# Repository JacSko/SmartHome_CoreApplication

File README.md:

# SmartHome CoreApplication

## Description
The idea of the project is to gain simple control over home appliance (like lighting).
Main board was desgined to use STM32F411CEU MCU. It communicates with other boards (list below) using different interfaces (I2C, OneWire, USART).
The main responsibility of this part of project is to ensure informations about current temperature and humidity and appliance state.

**Main board is connected with:**
- **Relays board** - equipped with 16 relays, supports either 12VDC and 230VAC switching. Board allows to e.g control light state in all rooms. Connection over I2C bus.
- **Inputs board** - board designed to handle 16 inputs (8x 12VDC, 8x 230VAC). Connection over I2C bus with interrupt fired on each input state changed. The bouncing of inputs state has been resolved either by adding debouce capacitor and programatically, by delaying inputs state readout.
- **LED's board** - board equipped with 16 outputs to control led ambient light on staircase placed near to steps. It allows to achieve some lighting effects since can be controlled independently.
- **Sensors board** - Board, where temperature and humidity sensors (DHT11/DHT22 - type is auto-detected in application), also light intense sensor is connected. The communication is realized over OneWire interface, when light intense sensor signal is send in pure analogue form.

## Details
This module is not able to present gathered data.
There is another project [SmartHome_RPi](https://github.com/JacSko/SmartHome_RPi) responsible for presenting received data.
The communication with CoreApplication can be done in two ways:
- **Over WiFi** - ESP01 module is onboard, on startup it creates TCP server, where the RaspberryPi can connects and gets the data. Messages are send in raw bytes mode (for protocol specification see notification_manager.h)
- **Over Bluetooth** - this channel is desgined mainly to provide debug traces, but there are several commands that can be issued in string-based, human readable form (see doc/ dirextory for documntation details)

Project build is managed by CMake.
Core application was prepared using CMSIS bare-metal library without dependencies to external libraries (only appropriate header files are required, but those are part of repository).
Project contains also unit tests, where the original MCU header files has been stubbed to allow compilation.

## Building
### Building for target
To build binary, You need to have:
- the arm-none-eabi toolchain
- The st-linkv2 drivers (can be compiled from sources)
- The ST-FLASH utility installed
Once all of those step are ready:
```
cd <project_dir>
mkdir build && cd build
cmake ..
make
```
After the binary can be flashed by issuing:
```
make write
```
### Building Simulation
For details how to use this target, see [SmartHome_Tests](https://github.com/JacSko/SmartHome_Tests)
```
cd <project_dir>
mkdir build_sim
cd build_sim
cmake .. -DSIMULATION=On
make
```
### Building Unit tests
To build unit test, You have to clone googletest repo:
```
cd <project_dir>
cd ext_lib/googletest
git clone https://github.com/google/googletest.git
```
Than run script:
```
./build_and_run_ut.sh
```
### Coverage calculation
Run script:
```
./build_and_run_coverage.sh
```
HTML report will be opened automatically in Firefox, but it can be also found:
```
build_ut/html/coverage.html
```
## TODO
- [ ] EEPROM handling
- [ ] Settings rework to allow read/write settings from EEPROM
- [ ] ADC driver (power supply voltage, light intensity)
- [ ] Flashing over UART (from RaspberryPi module)

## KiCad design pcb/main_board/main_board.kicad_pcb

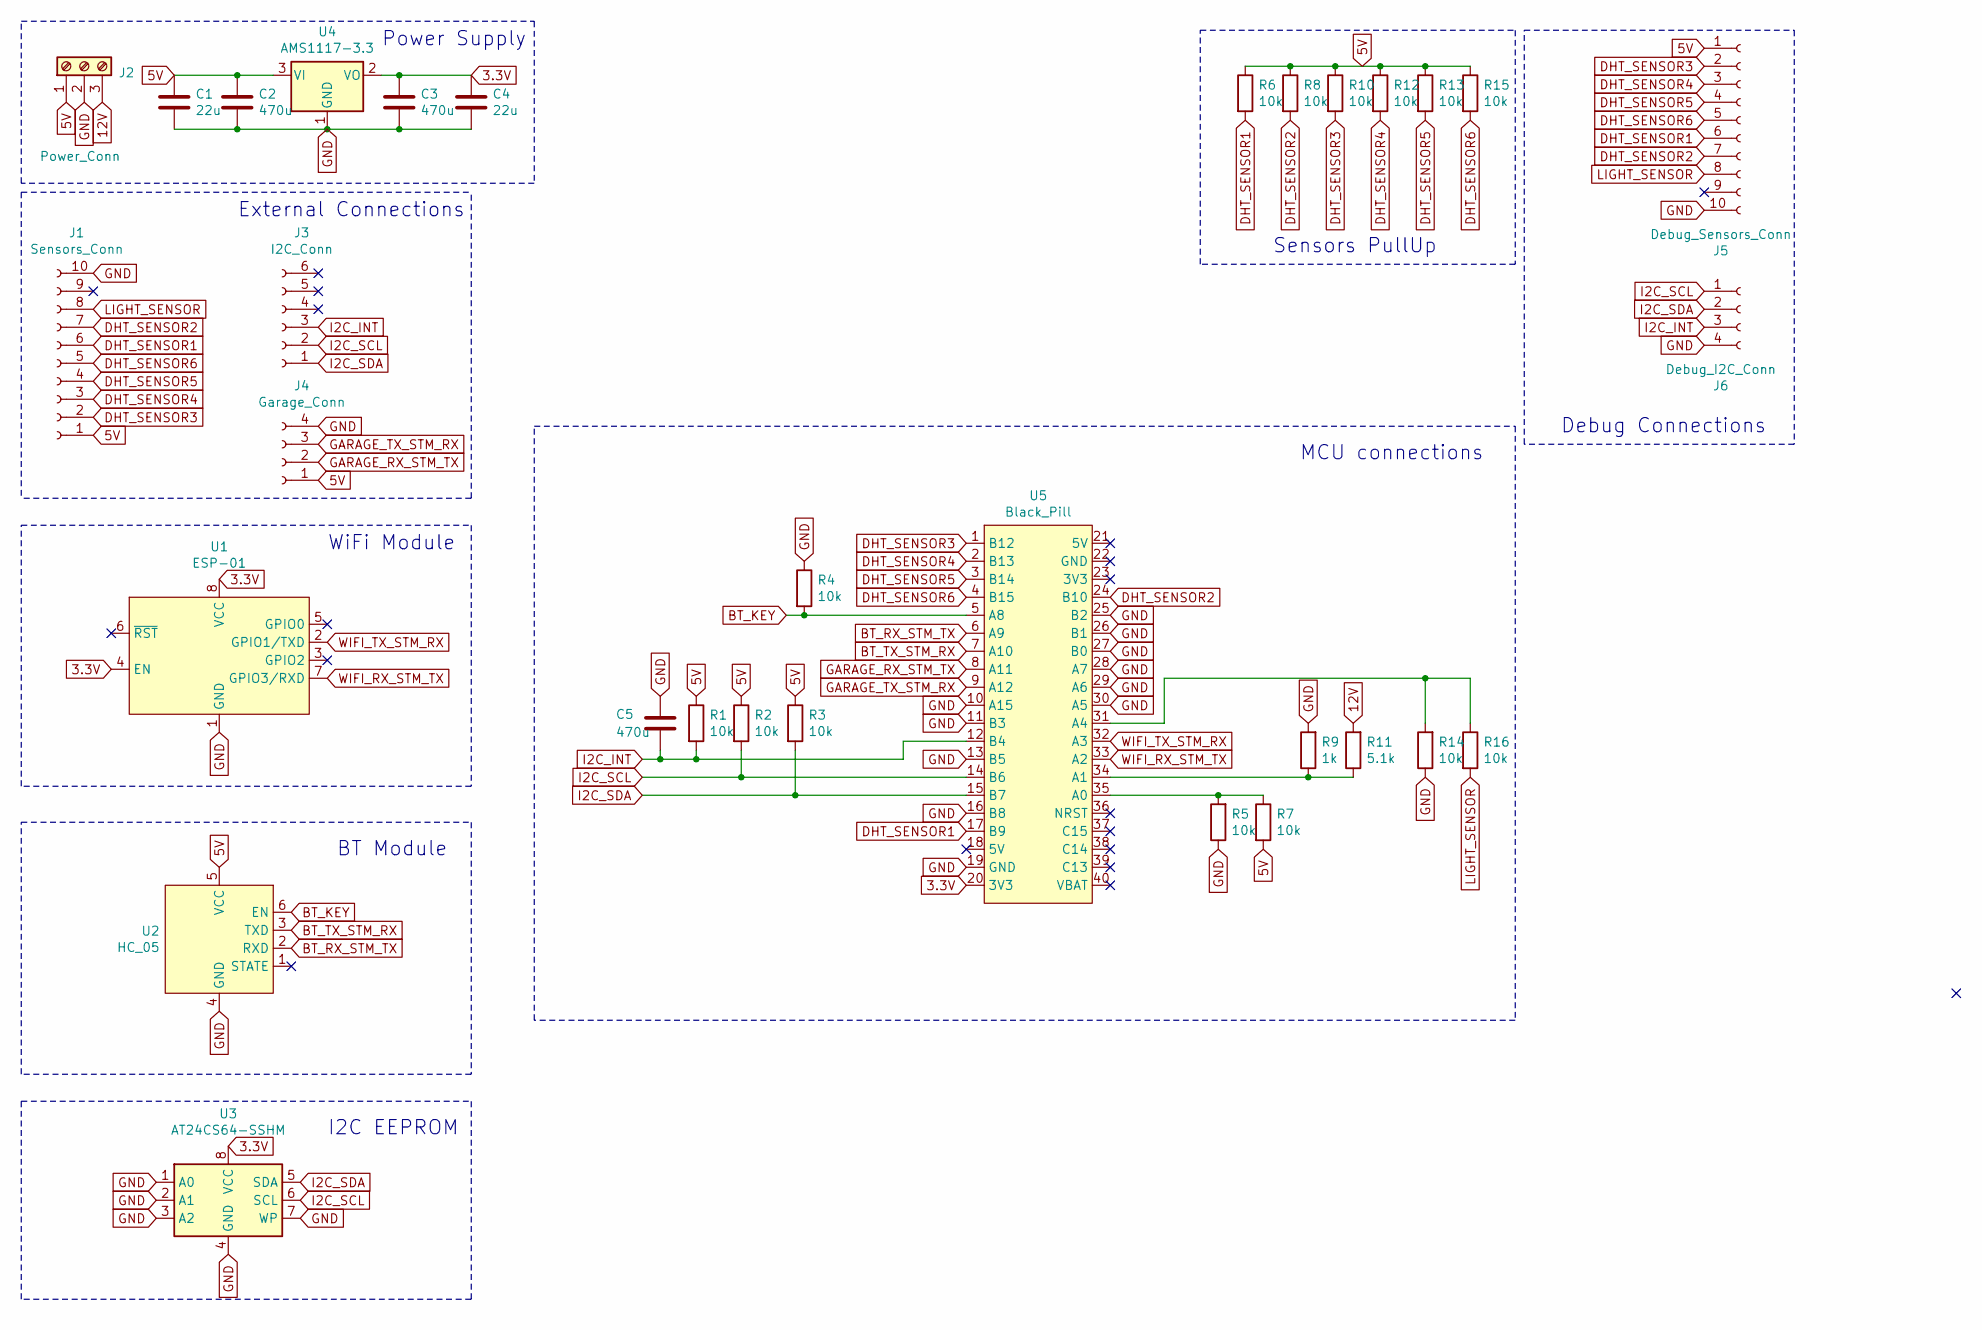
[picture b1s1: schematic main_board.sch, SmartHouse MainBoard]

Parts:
C1, C4: 22u; CP_EIA-7343-31_Kemet-D_Pad2.25x2.55mm_HandSolder
C2, C3, C5: 470u; CP_Radial_D8.0mm_P2.50mm
J1: Sensors_Conn; PinHeader_1x10_P2.54mm_Vertical
J2: Power_Conn; TerminalBlock_bornier-3_P5.08mm
J3: I2C_Conn; IDC-Header_2x03_P2.54mm_Vertical
J4: Garage_Conn; PinHeader_1x04_P2.54mm_Vertical
J5: Debug_Sensors_Conn; PinHeader_1x10_P2.54mm_Vertical
J6: Debug_I2C_Conn; PinHeader_1x04_P2.54mm_Vertical
R1, R2, R3, R4, R5, R6, R7, R8, R10, R12, R13, R14, R15, R16: 10k; R_1206_3216Metric_Pad1.30x1.75mm_HandSolder
R9: 1k; R_1206_3216Metric_Pad1.30x1.75mm_HandSolder
R11: 5.1k; R_1206_3216Metric_Pad1.30x1.75mm_HandSolder
U1: ESP-01; ESP01
U2: HC_05
U3: AT24CS64-SSHM; SOIC-8_3.9x4.9mm_P1.27mm
U4: AMS1117-3.3; SOT-223-3_TabPin2
U5: Black_Pill; Black_pill

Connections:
3.3V: C3.1, C4.1, U1.4 (EN), U1.8 (VCC), U3.8 (VCC), U4.2 (VO), U5.20 (3V3)
5V: C1.1, C2.1, J1.1, J2.1, J4.1, J5.1, R1.1, R2.1, R3.1, R6.1, R7.2, R8.1, R10.1, R12.1, R13.1, R15.1, U2.5 (VCC), U4.3 (VI)
12V: J2.3, R11.2
BT_KEY: R4.2, U2.6 (EN), U5.5 (A8)
BT_RX_STM_TX: U2.2 (RXD), U5.6 (A9)
BT_TX_STM_RX: U2.3 (TXD), U5.7 (A10)
DHT_SENSOR1: J1.6, J5.6, R6.2, U5.17 (B9)
DHT_SENSOR2: J1.7, J5.7, R8.2, U5.24 (B10)
DHT_SENSOR3: J1.2, J5.2, R10.2, U5.1 (B12)
DHT_SENSOR4: J1.3, J5.3, R12.2, U5.2 (B13)
DHT_SENSOR5: J1.4, J5.4, R13.2, U5.3 (B14)
DHT_SENSOR6: J1.5, J5.5, R15.2, U5.4 (B15)
GARAGE_RX_STM_TX: J4.2, U5.8 (A11)
GARAGE_TX_STM_RX: J4.3, U5.9 (A12)
GND: C1.2, C2.2, C3.2, C4.2, C5.1, J1.10, J2.2, J4.4, J5.10, J6.4, R4.1, R5.1, R9.2, R14.1, U1.1 (GND), U2.4 (GND), U3.1 (A0), U3.2 (A1), U3.3 (A2), U3.4 (GND), U3.7 (WP), U4.1 (GND), U5.10 (A15), U5.11 (B3), U5.13 (B5), U5.16 (B8), U5.19 (GND), U5.25 (B2), U5.26 (B1), U5.27 (B0), U5.28 (A7), U5.29 (A6), U5.30 (A5)
I2C_INT: C5.2, J3.3, J6.3, R1.2, U5.12 (B4)
I2C_SCL: J3.2, J6.1, R2.2, U3.6 (SCL), U5.14 (B6)
I2C_SDA: J3.1, J6.2, R3.2, U3.5 (SDA), U5.15 (B7)
LIGHT_SENSOR: J1.8, J5.8, R16.2
unnamed: R5.2, R7.1, U5.35 (A0)
unnamed: R9.1, R11.1, U5.34 (A1)
unnamed: R14.2, R16.1, U5.31 (A4)
WIFI_RX_STM_TX: U1.7 (GPIO3/RXD), U5.33 (A2)
WIFI_TX_STM_RX: U1.2 (GPIO1/TXD), U5.32 (A3)

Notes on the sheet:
WiFi Module
BT Module
I2C EEPROM
Debug Connections
Sensors PullUp
MCU connections
External Connections
Power Supply

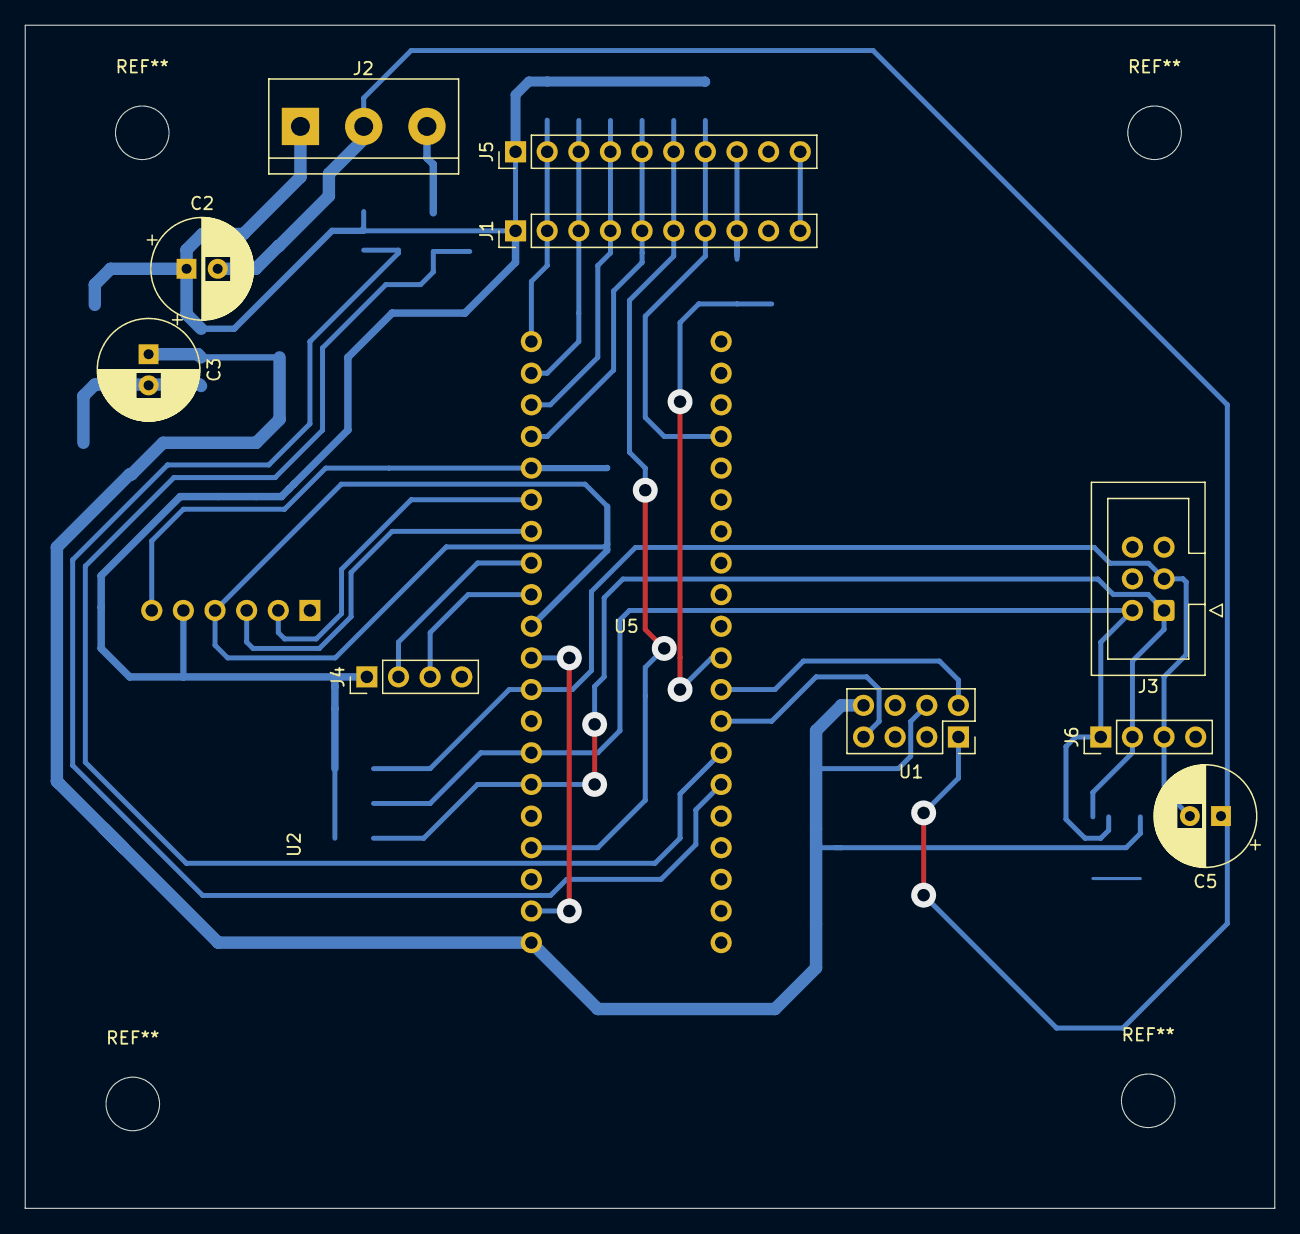
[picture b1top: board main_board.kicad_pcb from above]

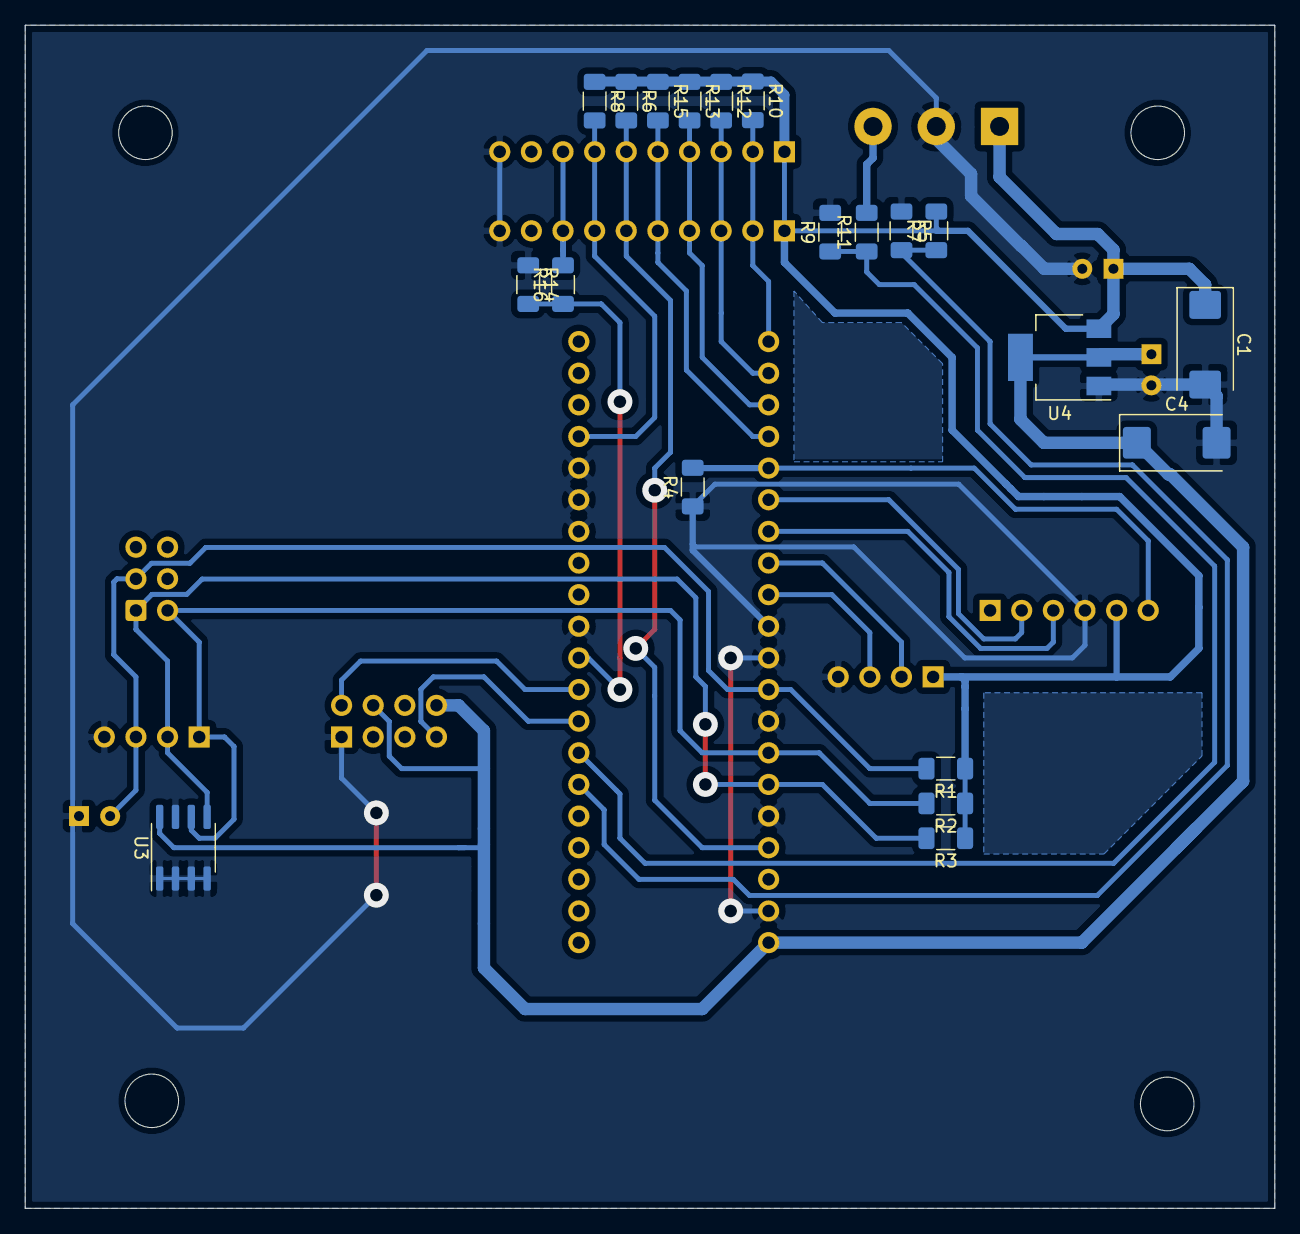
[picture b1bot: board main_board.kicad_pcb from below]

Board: 2 copper layers, 100.3 x 95.0 mm, 32 parts (20 on the bottom side), 24 nets.

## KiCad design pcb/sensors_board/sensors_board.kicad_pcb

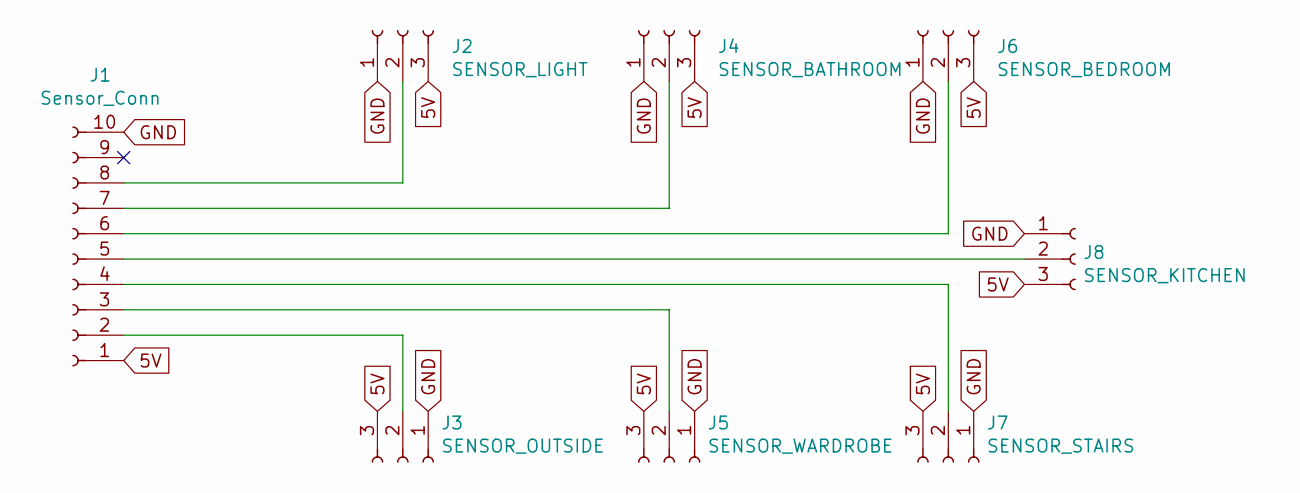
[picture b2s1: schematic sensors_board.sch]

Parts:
J1: Sensor_Conn; PinHeader_1x10_P2.54mm_Vertical
J2: SENSOR_LIGHT; TerminalBlock_bornier-3_P5.08mm
J3: SENSOR_OUTSIDE; TerminalBlock_bornier-3_P5.08mm
J4: SENSOR_BATHROOM; TerminalBlock_bornier-3_P5.08mm
J5: SENSOR_WARDROBE; TerminalBlock_bornier-3_P5.08mm
J6: SENSOR_BEDROOM; TerminalBlock_bornier-3_P5.08mm
J7: SENSOR_STAIRS; TerminalBlock_bornier-3_P5.08mm
J8: SENSOR_KITCHEN; TerminalBlock_bornier-3_P5.08mm

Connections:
5V: J1.1, J2.3, J3.3, J4.3, J5.3, J6.3, J7.3, J8.3
GND: J1.10, J2.1, J3.1, J4.1, J5.1, J6.1, J7.1, J8.1
unnamed: J1.2, J3.2
unnamed: J1.3, J5.2
unnamed: J1.4, J7.2
unnamed: J1.5, J8.2
unnamed: J1.6, J6.2
unnamed: J1.7, J4.2
unnamed: J1.8, J2.2

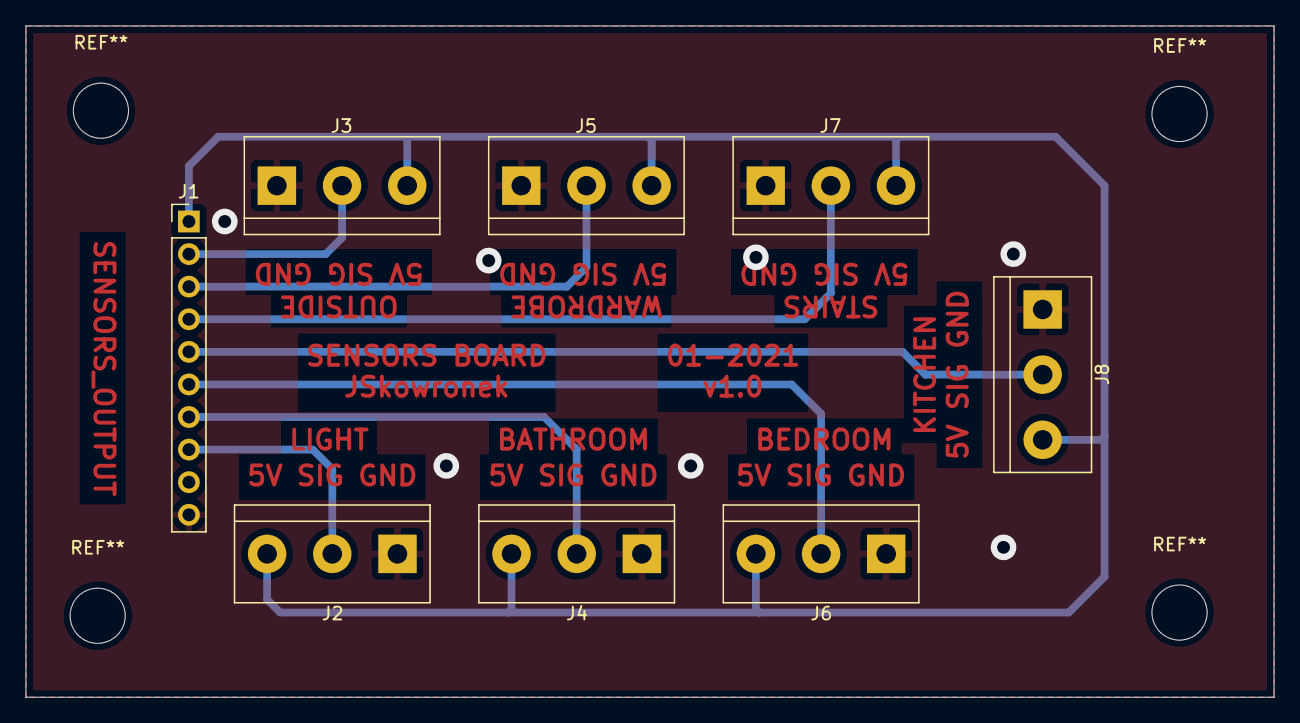
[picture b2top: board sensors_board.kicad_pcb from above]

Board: 2 copper layers, 97.3 x 52.3 mm, 8 parts (0 on the bottom side), 9 nets.

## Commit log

2020-10-30 Initial commit
    Two build targets (STM and UT) are working
2020-10-30 UT framework added
2020-10-31 Added stm stubs and build target "make coverage"
2020-10-31 gitignore update
2020-10-31 Fix for coverage branches, bash scripts file created
2020-10-31 bash scripts added, removed coverge target from CMake
2020-11-01 uartengine started, stm stub reworked
2020-11-01 gpio_libMock added
2020-11-01 uartengine moved to drivers module
2020-11-02 Added UT for uartengine, main function prepared to HW tests
2020-11-02 disable all interrupt when writing data to uart buffer
2020-11-04 uartengine tested, CR LF ending case added
2020-11-06 TIME module added
2020-11-10 generic list added, utilities created, syscalls added
2020-11-11 Fix for time_counter
2020-11-14 task_scheduler implementation added
2020-11-15 added test for task_scheduler to reach 80% BC
2020-11-15 UART_ENGINE ignores CR and calls callback only if received strlen is greated than 0
2020-11-15 fix uart_engine compile warning
2020-11-18 wifi driver implementing started
2020-11-22 uartengine now allows to check for string in synchronous way
2020-11-24 development of wifi_driver
2020-11-24 tiny string formatter added
2020-11-27 Fix for receiving UART data
2020-11-27 Wifi driver implementation - next part
2020-11-28 uart engine ready to notify about received strings and bytes
2020-11-28 uartengine mock updated to latest changes
2020-11-28 wifi driver development
2020-11-28 HW checkout, increased wait time for OK response when connecting to wireless network
2020-11-30 WiFi driver now use USART2, BT engine use USART1, Wifi interface description added, not needed inclusions removed
2020-11-30 BT engine mock added
2020-12-01 Logger development started
2020-12-01 fix for building UT after creating bt_engine
2020-12-01 Now UT build does not build unnecessary targets
2020-12-03 Logger module development
2020-12-03 fix for reading time from NTP server
2020-12-03 Mock targets now includes header files, logger mock added
2020-12-04 Logger rework - allow variable argument, possible fix for reading data from NTP, uartengine tests developed
2020-12-05 LOG_ERROR is now enabled by default, wifi_driver debugs added
2020-12-05 wifi_reset() added to wifi driver
2020-12-05 wifi_driver mock added
2020-12-05 added func to set time from UTC, received from NTP server
2020-12-05 test commit
2020-12-05 Added time_wait function
2020-12-05 ut aligned to latest changes is modules
2020-12-06 first version of wifi manager added
2020-12-06 Mock targets moved to test directories, some mocks changed from interface to static libraries
2020-12-06 fix for getClientDetails, added function to get max number of clients
2020-12-06 Logger changed to allows registering more than one sender function
2020-12-08 Workaround for reading NTP time at initialization stage
2020-12-08 Removed logger from wifi_driver, wifi manager tests added
2020-12-08 Add logging to task scheduler
2020-12-08 Cleanup TODOs
2020-12-08 system_settings added for wifi_manager
2020-12-08 Revert "system_settings added for wifi_manager"
    This reverts commit b045bd4f0136ec413c926a97fa75ef98edfd90f5.
2020-12-10 Fix for receiving data from socket
2020-12-10 uartengine now uses config from init instead of hardcoded
2020-12-13 command parser development, wifimgr commands added
2020-12-13 get_ntp_server and get_server_port functions added to WIFIMGR
2020-12-13 command parser test for WIFIMGR
2020-12-13 Documentation - added commands for wifimgr
2020-12-13 doxyfile and source/header templated added
2020-12-13 command parser adjusted to doxygen, templates updated
2020-12-13 drivers doxygen adding in progress
2020-12-14 Doxygen added for drivers
2020-12-14 Doxygen for Logger added
2020-12-14 Doxygen for Task Scheduler added
2020-12-14 Doxygen for Time module added
2020-12-14 Doxygen for Utilities added
2020-12-14 example module created, with templates of source and header
2020-12-14 string_formatter precision handling, documentation updated
2020-12-15 string formatter functions renamed, string formatter tests added
2020-12-15 String formatter - removed format_length function
2020-12-15 documentation update
2020-12-15 Fix for precise formatting, Logger date and time formatting changed
2020-12-15 DHT driver skeleton added
2020-12-15 DHT driver development
2020-12-16 fix for logger tests after formatting change
2020-12-16 Priority handling added to time and scheduler modules
2020-12-17 dht development end - unit tests added
2020-12-17 fixes for valgrind issues
2020-12-17 DHT driver cleanup
2020-12-17 some major fixes to dht driver and scheduler
2020-12-17 LOG_DHT_DRV added, debugs to dht_driver added
2020-12-17 dht_driver_mock added
2020-12-18 I2C skeleton added
2020-12-18 ods documentation update
2020-12-18 i2c driver development
2020-12-18 i2c driver development end
2020-12-19 debugs added to I2C driver
2020-12-19 app DHT driver change in runtime
2020-12-19 little cleanup in i2c driver
2020-12-19 i2c driver UT added
2020-12-20 i2c driver removed not needed debug
2020-12-22 Inputs module added, UT added, documentation updated
2020-12-22 interface for relays_board added
2020-12-22 added new function in inputs_board
2020-12-26 relays module first implementation added
2020-12-27 relays debugs added
2020-12-27 gpio_lib merged to drivers
2020-12-27 env module interface added
2020-12-27 env module development
2020-12-27 relays and inputs shortly tested
2020-12-28 env module added
2020-12-28 bathroom fan skeleton added
2020-12-29 fan module added
2020-12-29 dexygen doc updated
2020-12-30 added function to read inputs directly from board
2020-12-30 rel_read_all function added to read relays directly from board
2020-12-30 read relays state on startup
2020-12-30 stairs led module skeleton added
2021-01-06 stairs led module implementation ongoing
2021-01-09 SLM development end
2021-01-10 added methods to send bytes over UART
2021-01-10 main_board schematic added
2021-01-11 PCB layout added
2021-01-12 Main board PCB updated
2021-01-12 Sensors board added
2021-01-15 small boards update
2021-01-16 main_baord reworked to one-side board
2021-01-17 command parser commands development
2021-01-18 command parser development
2021-01-18 command parser development ready
2021-01-18 added UT for logger
2021-01-18 added set program function to slm module
2021-01-18 added set_program from SLM to command parser
2021-01-18 Added commands to documentation
2021-01-18 fix for command parser tests
2021-01-19 added system reset method
2021-01-20 small fixes after HW check
2021-01-21 Added new timestamp module - to allow safe awaiting for events without systick influence.
2021-01-22 checkout
2021-01-22 common types extracted to separate directory - ready to covert to submodule
2021-01-22 removed SmartHomeTypes dir
2021-01-22 added SmartHomeTypes submodule
2021-01-22 added notification_manager skeleton
2021-01-22 google test removed form repository
2021-02-12 Readme initial version
2021-02-12 Readme update
2021-02-12 Removed old documentation file
2021-02-12 rework of notification manager
2021-02-12 SHT bump
2021-02-12 mocks update after listeners changes
2021-02-12 ntfmgr init completed using listeners
2021-02-12 added env_get_sensor_data function
2021-02-12 added functions to send bytes using wifi_manager
2021-02-12 preparing main to use define's
2021-02-12 notification_manager interface added
2021-02-12 ut fot system_timestamp added
2021-02-12 listeners feature added to fan module
2021-02-12 notification_manager development
2021-02-12 main function use defines
2021-02-12 NTF manager development, SHT bump
2021-02-12 listeners feature added to SLM, tests cleanup
2021-02-12 added function to broadcast data over WiFi
2021-02-12 listeners feature added to relays module
2021-02-12 fix for branch coverage calculations
2021-02-12 added simple init to ntfmgr
2021-02-12 CMake preparation for simulation target
2021-02-13 global settings moved to separate file
2021-02-13 fix for main startup, DHT sensr match corrected
2021-02-15 add get_config function to ENV module
2021-02-15 Added handling of SYSTEM_STATUS NTF_GET command
2021-02-16 FAN status added to system_status message
2021-02-16 small rework of notification manager
2021-02-16 fix for reading data from application
2021-02-17 use write_to_buffer instead of direct operation on buffer
2021-02-17 notification manager reworked to send data as string
2021-02-17 added handling od string-based request to notification manager
2021-02-18 fix for implicit function declaration
2021-02-20 SCH, TS, TIME stubs added
2021-02-20 BT engine stubbing in progress
2021-02-21 On SLM program start, it is required to power the leds via relay
2021-02-21 Fix for calculating bytes to send via I2C
2021-02-21 all modules enabled in main
2021-02-21 Improvement for calculating time in scheduler
2021-02-21 btengine stub added
2021-02-21 sender handling added to logger again
2021-02-22 added init version of socket_driver
2021-02-22 added LOG_SIM to logger, add -DSIMULATION to SIMULATION arget
2021-02-22 fix to logger crash after adding LOG_SIM group
2021-02-22 fix for assigning sock_id in socket_driver
2021-02-22 BT engine stub reworked to use socket_driver
2021-02-23 HW_STUB interface added
2021-02-23 first implementation of hw_stub added
2021-02-25 HW stub development, I2C driver SIM version prepared
2021-02-25 DHT driver SIM version added
2021-02-25 Unit tests added for DHT sim implementation
2021-02-25 message parsing for I2C stub added
2021-02-26 interrupt handling moved outside of inputs module
2021-02-27 dht, i2c sim versions ready, Cmakes cleanup
2021-02-27 wifi driver sim added, stm stubs updated
2021-02-27 switched SIM to main.c file, fix for crash in ENV module
2021-02-27 Fix for I2C tests after change the default stub state
2021-02-27 fix interrupt handling for inputs module
2021-02-27 enable all logger groups for simulation
2021-02-28 SLM programs timings updated
2021-02-28 little cleanup in hw_stub
2021-02-28 config settings reworked, removed logs over wifi feature
2021-02-28 settings reworked - moved to common project space
2021-02-28 fix for SLM tests
2021-03-05 fix for wrong debug trace in hw_stub.c
2021-03-05 DHT types moved to common space, SHT bump
2021-03-05 Socket driver rework - use header before message, SHT bump
2021-03-09 Changed time base from 100 to 10 ms
2021-03-09 Changed socket hang-up timeout to 100ms, some cleanup
2021-03-09 Newline removed from logs after changing socket sending strategy (size-based)
2021-03-09 Move ENV_MEASURE_PERIOD to common space
2021-03-09 add error log when cannot set LED step timeout
2021-03-09 Added new command 'rel set <rel> <state>
2021-06-08 Added handling of system version command
2021-06-08 Added google tests as submodule
